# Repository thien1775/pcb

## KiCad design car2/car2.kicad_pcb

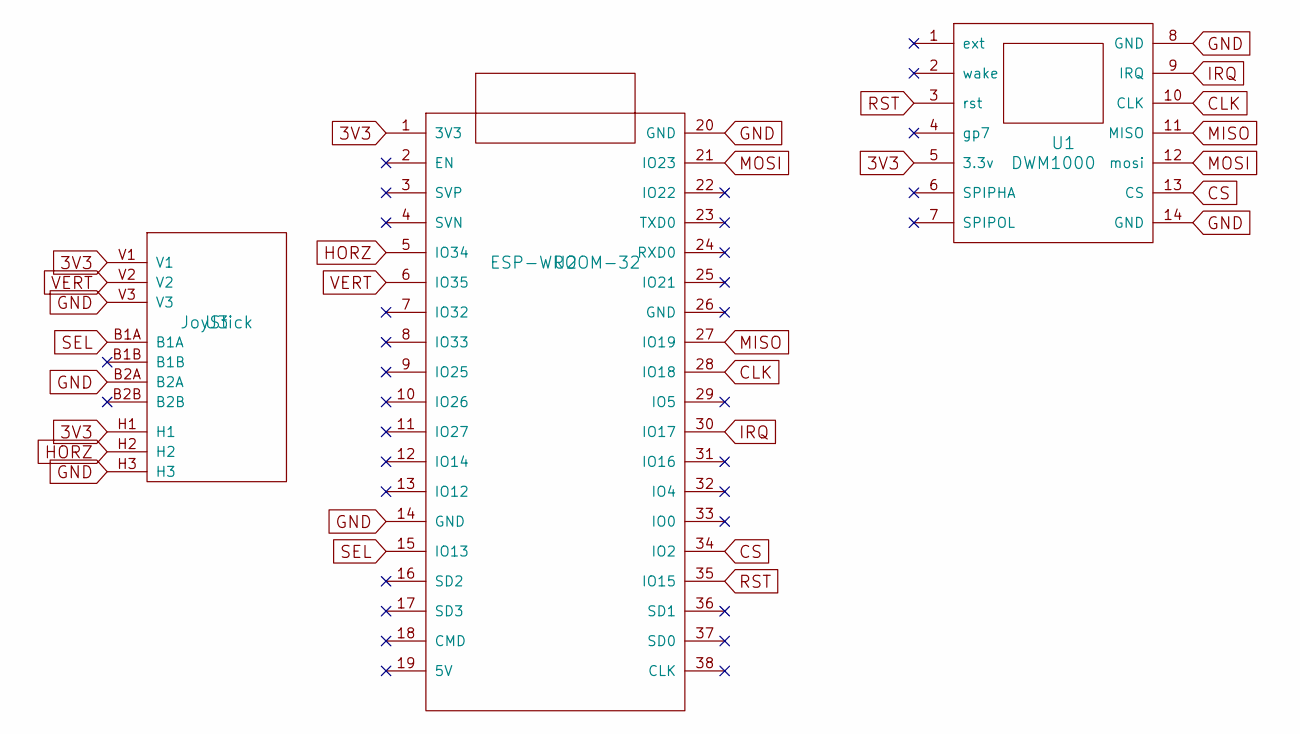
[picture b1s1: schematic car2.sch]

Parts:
U1: DWM1000
U2: ESP-WROOM-32; ESP-VROOM-32
U3: JoyStick; JOYSTICK

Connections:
3V3: U1.5 (3.3v), U2.1 (3V3), U3.H1, U3.V1
CLK: U1.10 (CLK), U2.28 (IO18)
CS: U1.13 (CS), U2.34 (IO2)
GND: U1.8 (GND), U1.14 (GND), U2.14 (GND), U2.20 (GND), U3.B2A, U3.H3, U3.V3
HORZ: U2.5 (IO34), U3.H2
IRQ: U1.9 (IRQ), U2.30 (IO17)
MISO: U1.11 (MISO), U2.27 (IO19)
MOSI: U1.12 (mosi), U2.21 (IO23)
RST: U1.3 (rst), U2.35 (IO15)
SEL: U2.15 (IO13), U3.B1A
VERT: U2.6 (IO35), U3.V2

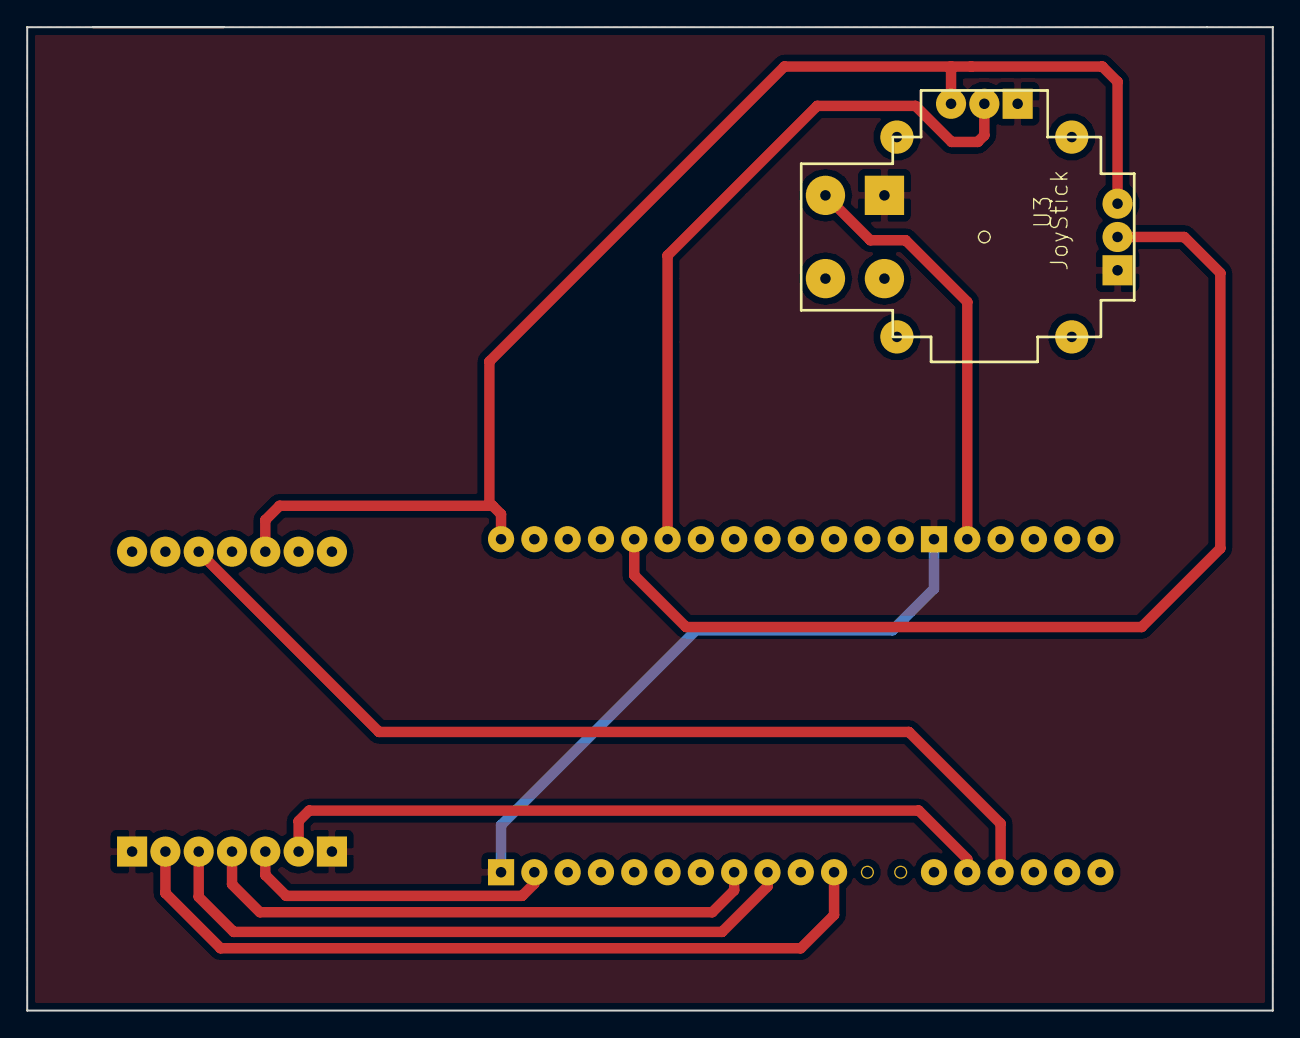
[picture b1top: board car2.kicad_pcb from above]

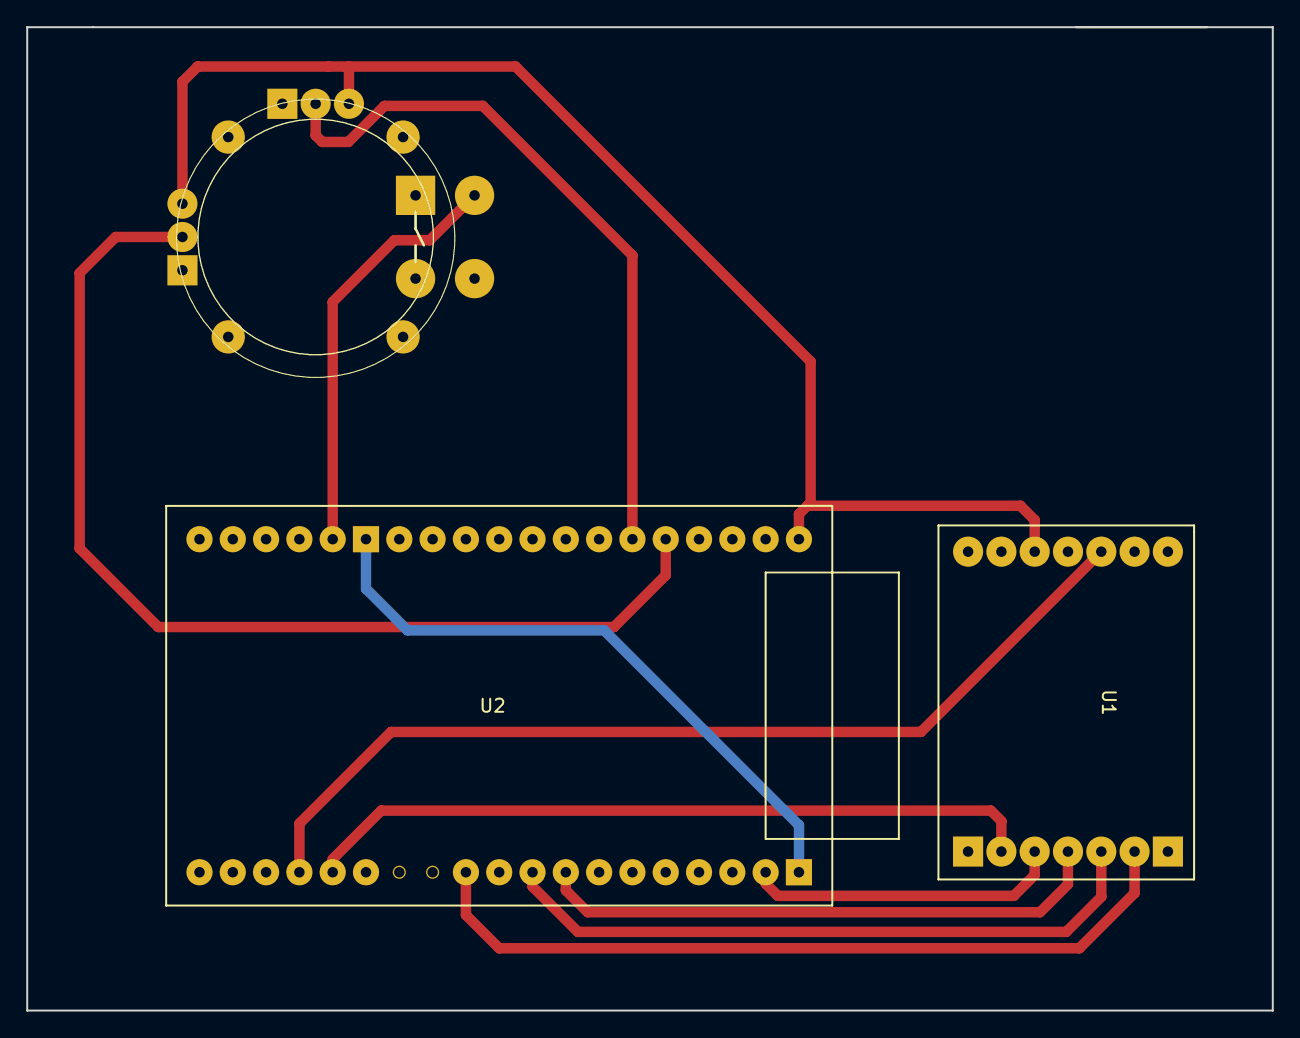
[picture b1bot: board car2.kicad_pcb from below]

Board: 2 copper layers, 95.0 x 75.0 mm, 3 parts (3 on the bottom side), 11 nets.

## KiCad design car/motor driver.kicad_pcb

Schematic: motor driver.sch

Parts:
P1: CONN_01X08; Pin_Header_Straight_1x08
P2, P3, P4: CONN_01X02; TerminalBlock_Pheonix_MPT-2.54mm_2pol
Q1, Q2: PN2222A; TO-92_Molded_Narrow
R1, R3: 1K; Resistor_Horizontal_RM10mm
R2, R4: 10K; Resistor_Horizontal_RM10mm
U1: L293D; DIP-16_W7.62mm

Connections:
/D1: P1.2, R1.2, U1.2
/D1/: Q1.3, R2.1, U1.7
/D2: P1.7, R3.2, U1.15
/D2/: Q2.3, R4.2, U1.10
/E1: P1.1, U1.1
/E2: P1.8, U1.9
/O1: P2.1, U1.3
/O2: P2.2, U1.6
/O3: P3.1, U1.11
/O4: P3.2, U1.14
GND: P1.5, P1.6, P4.2, Q1.1, Q2.1, U1.4, U1.5, U1.12, U1.13
unnamed: Q1.2, R1.1
unnamed: Q2.2, R3.1
VCC: P1.3, P1.4, R2.2, R4.1, U1.16
VDD: P4.1, U1.8

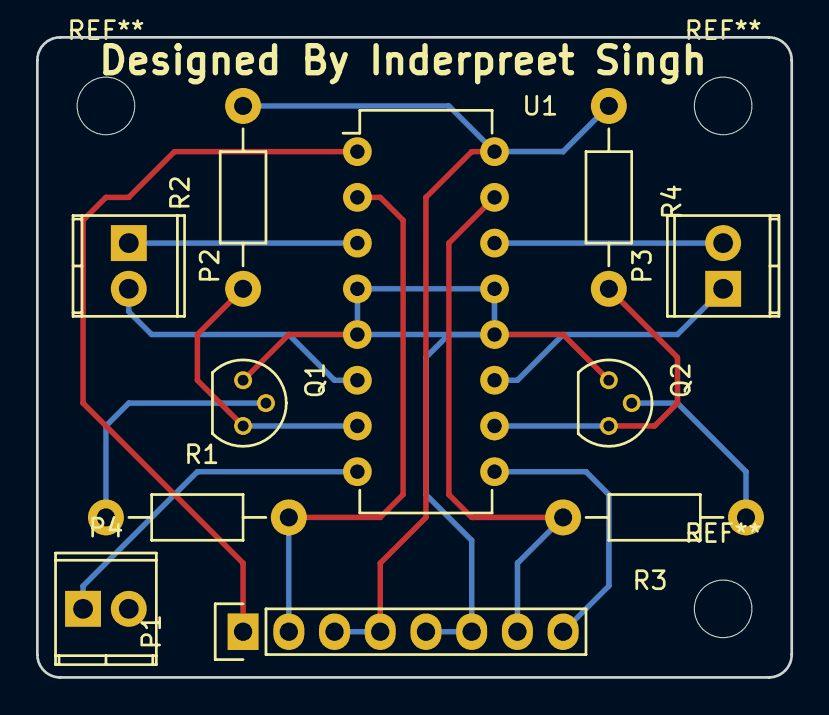
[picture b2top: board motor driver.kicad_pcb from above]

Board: 2 copper layers, 41.9 x 35.6 mm, 11 parts (0 on the bottom side), 15 nets.
